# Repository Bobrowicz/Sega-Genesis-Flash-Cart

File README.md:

# Sega Genesis Flash Cartridge
 This project is an attempt to create programmable cartridge for Sega Genesis system.  Project is based around two SST39SF040 4Mbit flash chips. Address bus is common to both chips, and data bus is split between the two into low and high byte.  Three position switch allows user to slelect between two 512kB banks or use entire 1MB capacity.
 
 Project has not been tested in real hardware.

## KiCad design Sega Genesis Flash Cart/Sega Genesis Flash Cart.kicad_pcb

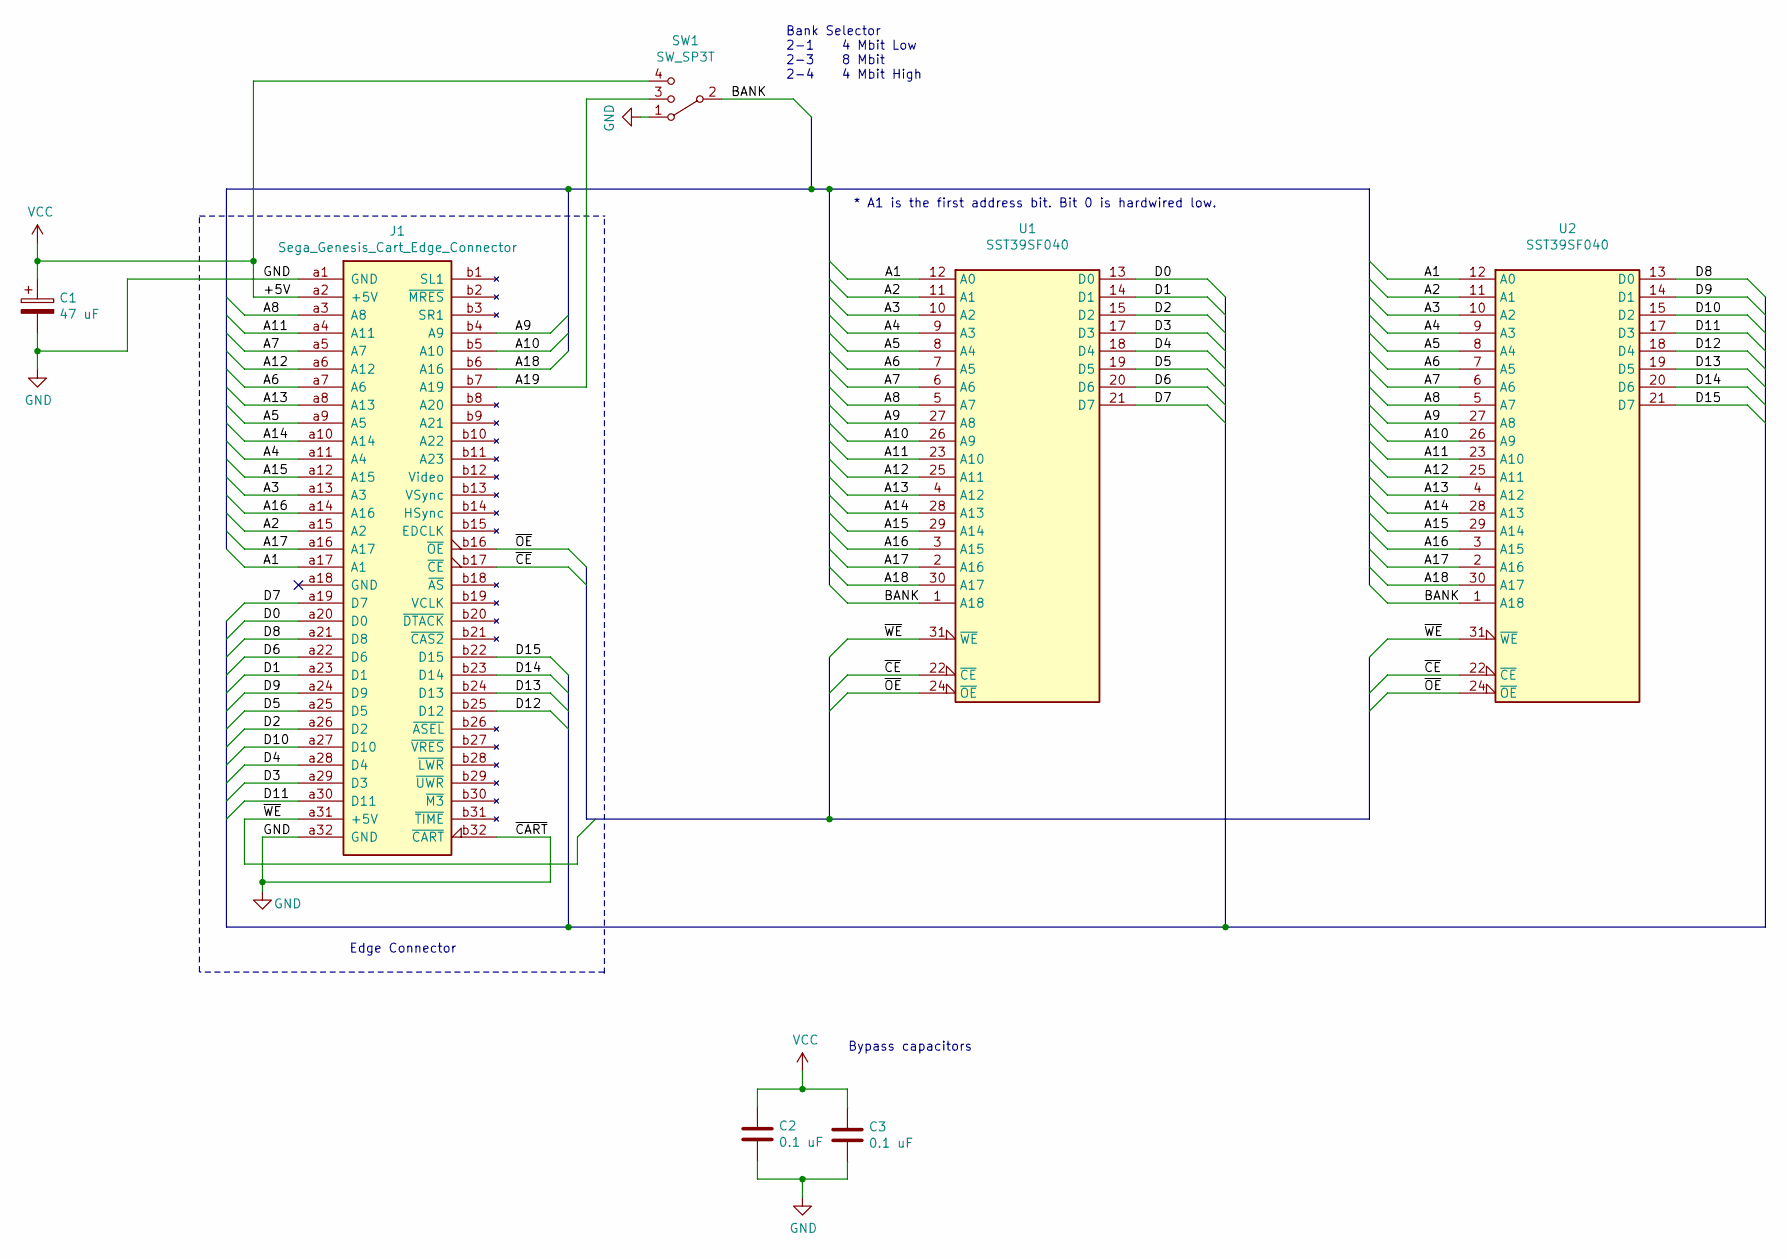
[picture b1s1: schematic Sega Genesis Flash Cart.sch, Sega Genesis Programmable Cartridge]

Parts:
C1: 47 uF; CP_Radial_D6.3mm_P2.50mm
C2, C3: 0.1 uF; C_Disc_D4.3mm_W1.9mm_P5.00mm
J1: Sega_Genesis_Cart_Edge_Connector; GENESIS-EDGE
SW1: SW_SP3T; MHS_133_Series_Switch
U1, U2: SST39SF040; DIP-32_W15.24mm

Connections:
/A1: J1.a17 (A1), U1.12 (A0), U2.12 (A0)
/A2: J1.a15 (A2), U1.11 (A1), U2.11 (A1)
/A3: J1.a13 (A3), U1.10 (A2), U2.10 (A2)
/A4: J1.a11 (A4), U1.9 (A3), U2.9 (A3)
/A5: J1.a9 (A5), U1.8 (A4), U2.8 (A4)
/A6: J1.a7 (A6), U1.7 (A5), U2.7 (A5)
/A7: J1.a5 (A7), U1.6 (A6), U2.6 (A6)
/A8: J1.a3 (A8), U1.5 (A7), U2.5 (A7)
/A9: J1.b4 (A9), U1.27 (A8), U2.27 (A8)
/A10: J1.b5 (A10), U1.26 (A9), U2.26 (A9)
/A11: J1.a4 (A11), U1.23 (A10), U2.23 (A10)
/A12: J1.a6 (A12), U1.25 (A11), U2.25 (A11)
/A13: J1.a8 (A13), U1.4 (A12), U2.4 (A12)
/A14: J1.a10 (A14), U1.28 (A13), U2.28 (A13)
/A15: J1.a12 (A15), U1.29 (A14), U2.29 (A14)
/A16: J1.a14 (A16), U1.3 (A15), U2.3 (A15)
/A17: J1.a16 (A17), U1.2 (A16), U2.2 (A16)
/A18: J1.b6 (A16), U1.30 (A17), U2.30 (A17)
/A19: J1.b7 (A19), SW1.3
/BANK: SW1.2, U1.1 (A18), U2.1 (A18)
/D0: J1.a20 (D0), U1.13 (D0)
/D1: J1.a23 (D1), U1.14 (D1)
/D2: J1.a26 (D2), U1.15 (D2)
/D3: J1.a29 (D3), U1.17 (D3)
/D4: J1.a28 (D4), U1.18 (D4)
/D5: J1.a25 (D5), U1.19 (D5)
/D6: J1.a22 (D6), U1.20 (D6)
/D7: J1.a19 (D7), U1.21 (D7)
/D8: J1.a21 (D8), U2.13 (D0)
/D9: J1.a24 (D9), U2.14 (D1)
/D10: J1.a27 (D10), U2.15 (D2)
/D11: J1.a30 (D11), U2.17 (D3)
/D12: J1.b25 (D12), U2.18 (D4)
/D13: J1.b24 (D13), U2.19 (D5)
/D14: J1.b23 (D14), U2.20 (D6)
/D15: J1.b22 (D15), U2.21 (D7)
/~CE: J1.b17 (~CE), U1.22 (~CE), U2.22 (~CE)
/~OE: J1.b16 (~OE), U1.24 (~OE), U2.24 (~OE)
/~WE: J1.a31 (+5V), U1.31 (~WE), U2.31 (~WE)
GND: C1.2, C2.2, C3.2, J1.a1 (GND), J1.a32 (GND), J1.b32 (~CART), SW1.1, U1.16 (GND), U2.16 (GND)
VCC: C1.1, C2.1, C3.1, J1.a2 (+5V), SW1.4, U1.32 (VCC), U2.32 (VCC)

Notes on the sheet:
Edge Connector
* A1 is the first address bit. Bit 0 is hardwired low.
Bypass capacitors
Bank Selector 2-1 4 Mbit Low 2-3 8 Mbit 2-4 4 Mbit High

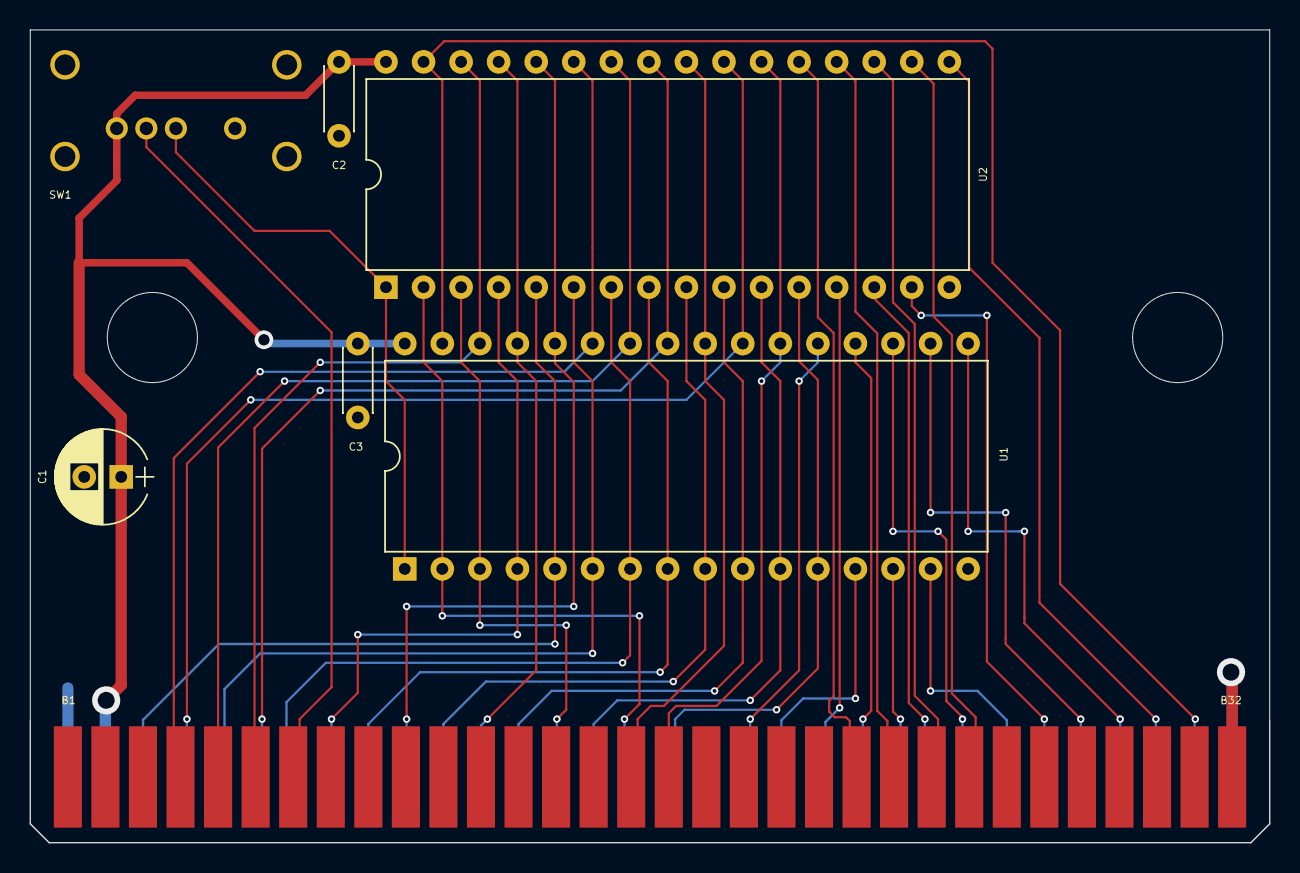
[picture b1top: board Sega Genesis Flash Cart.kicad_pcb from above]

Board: 2 copper layers, 83.8 x 54.9 mm, 7 parts (0 on the bottom side), 41 nets.

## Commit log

2020-10-04 Project start
    Gathered some documentation and started on cartridge schematic.
2020-10-04 Circuit schematic rev A
2020-10-04 Capacitor values
2020-10-11 Begin PCB layout
    Revised schematic, added footprints and strated PCB layout.
2021-02-20 PCB layout
2021-09-12 Revised PCB and schematic
    Changed schematic symbol for Genesis edge connector.
    Changed footprint for Genesis edge connector. Ripped all traces and re-routed the PCB.
